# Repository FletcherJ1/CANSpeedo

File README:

Purpose
OBD Case (ebay link / picture)
Picture of PCB design
Costs
Firmware etc
Hardware used.
Libraries used.
Picture of results
Open about current issues

Cars it currently works on

Instructions to use / get to work with car.

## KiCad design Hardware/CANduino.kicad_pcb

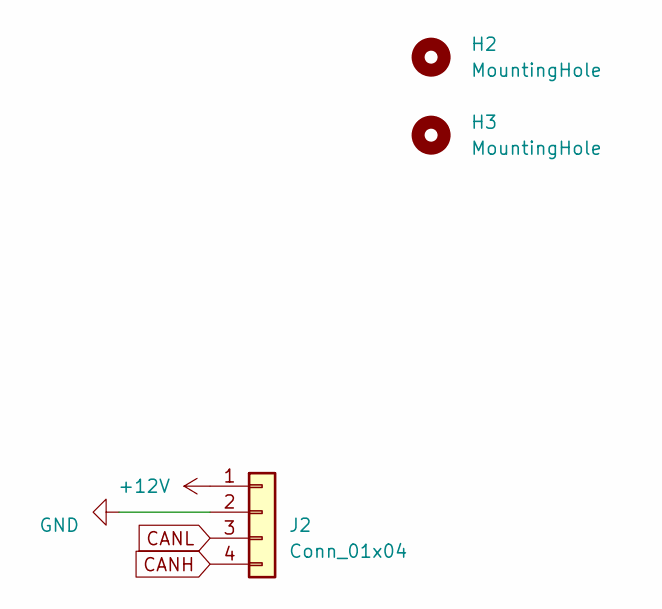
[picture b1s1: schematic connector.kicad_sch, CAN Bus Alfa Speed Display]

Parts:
H2, H3: MountingHole; MountingHole_6mm_Pad
J2: Conn_01x04; PinHeader_1x04_P1.27mm_Vertical

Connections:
+12V: J2.1; also elsewhere on the board
CANH: J2.4; also elsewhere on the board
CANL: J2.3; also elsewhere on the board
GND: J2.2; also elsewhere on the board

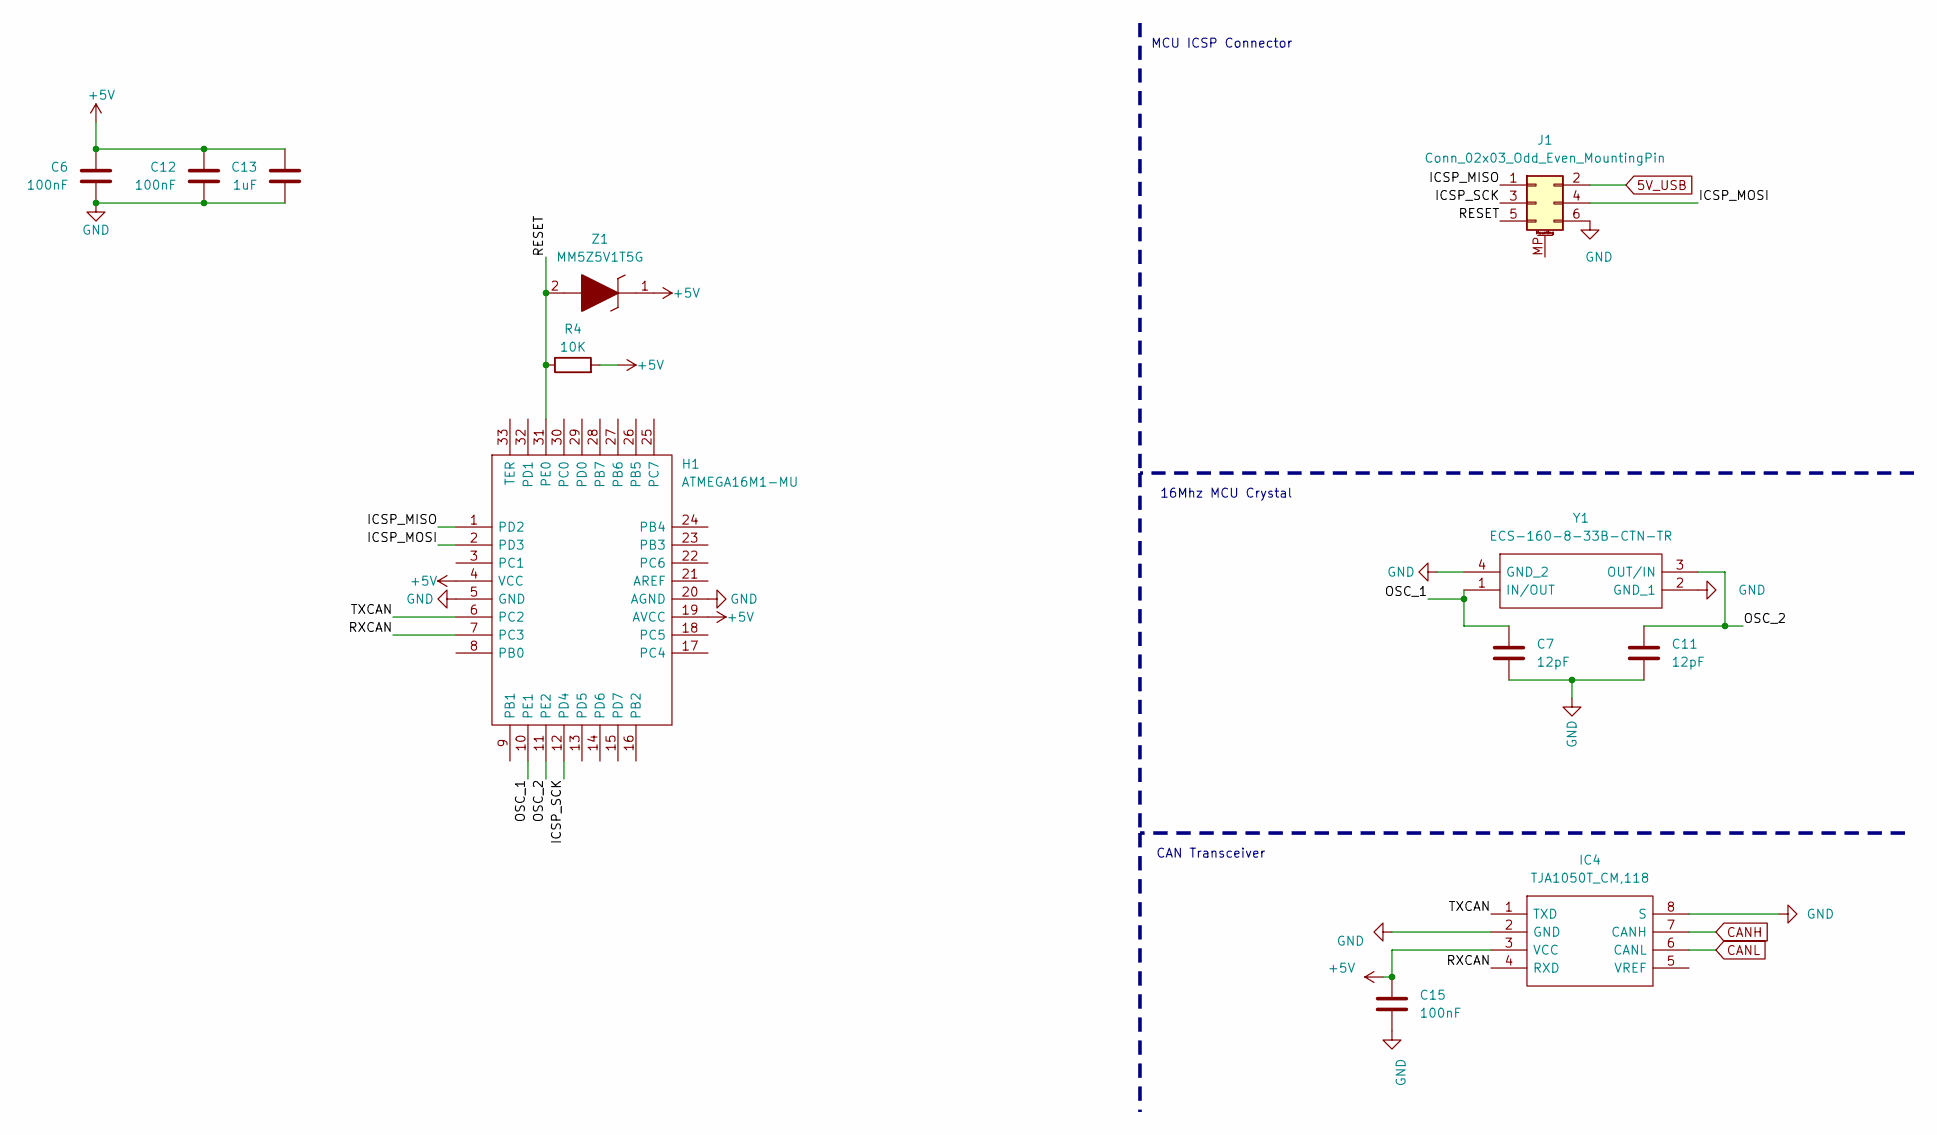
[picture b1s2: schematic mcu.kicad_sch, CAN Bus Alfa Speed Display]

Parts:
C6, C12, C15: 100nF; C_0603_1608Metric_Pad1.08x0.95mm_HandSolder
C7, C11: 12pF; C_0603_1608Metric_Pad1.08x0.95mm_HandSolder
C13: 1uF; C_0603_1608Metric_Pad1.08x0.95mm_HandSolder
H1: ATMEGA16M1-MU; QFN65P700X700X100-33N; Mouser Part Number 556-ATMEGA16M1-MU
IC4: TJA1050T_CM,118; SOIC127P600X175-8N; Mouser Part Number 771-TJA1050T/CM118
J1: Conn_02x03_Odd_Even_MountingPin; PinHeader_2x03_P2.54mm_Vertical
R4: 10K; R_0603_1608Metric_Pad0.98x0.95mm_HandSolder
Y1: ECS-160-8-33B-CTN-TR; ECS160833BCTNTR; Mouser Part Number 520-ECS160833BCTN-TR
Z1: MM5Z5V1T5G; SODFL1608X70N; Mouser Part Number 863-MM5Z5V1T5G

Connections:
5V_USB: J1.2; also elsewhere on the board
+5V: C6.2, C12.2, C13.2, C15.1, H1.4 (VCC), H1.19 (AVCC), IC4.3 (VCC), R4.2, Z1.1; also elsewhere on the board
/mcu/ICSP_MISO: H1.1 (PD2), J1.1
/mcu/ICSP_MOSI: H1.2 (PD3), J1.4
/mcu/ICSP_SCK: H1.12 (PD4), J1.3
/mcu/OSC_1: C7.1, H1.10 (PE1), Y1.1 (IN/OUT)
/mcu/OSC_2: C11.1, H1.11 (PE2), Y1.3 (OUT/IN)
/mcu/RESET: H1.31 (PE0), J1.5, R4.1, Z1.2
/mcu/RXCAN: H1.7 (PC3), IC4.4 (RXD)
/mcu/TXCAN: H1.6 (PC2), IC4.1 (TXD)
CANH: IC4.7 (CANH); also elsewhere on the board
CANL: IC4.6 (CANL); also elsewhere on the board
GND: C6.1, C7.2, C11.2, C12.1, C13.1, C15.2, H1.5 (GND), H1.20 (AGND), IC4.2 (GND), IC4.8 (S), J1.6, Y1.2 (GND_1), Y1.4 (GND_2); also elsewhere on the board

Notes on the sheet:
CAN Transceiver
MCU ICSP Connector
16Mhz MCU Crystal

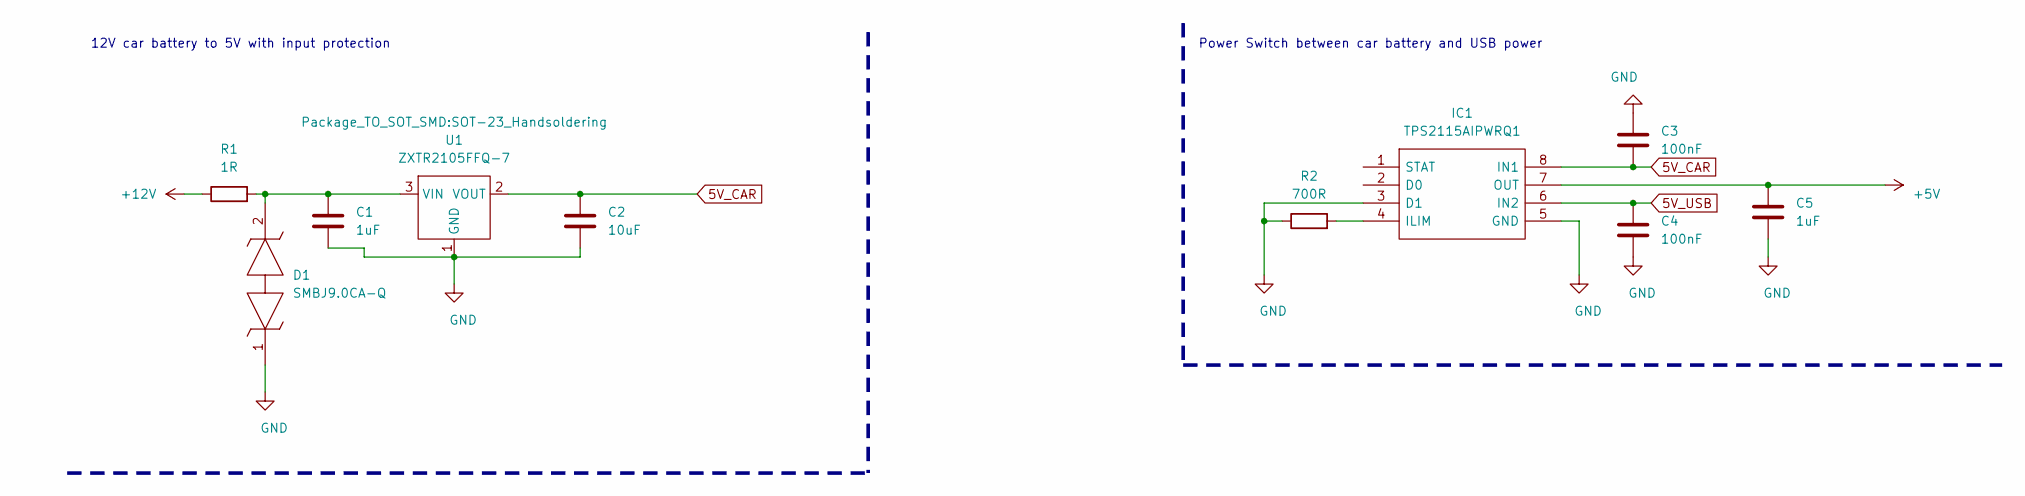
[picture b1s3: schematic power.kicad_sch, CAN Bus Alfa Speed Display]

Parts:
C1, C5: 1uF; C_0603_1608Metric_Pad1.08x0.95mm_HandSolder
C2: 10uF; C_0603_1608Metric_Pad1.08x0.95mm_HandSolder
C3, C4: 100nF; C_0603_1608Metric_Pad1.08x0.95mm_HandSolder
D1: SMBJ9.0CA-Q; DIONM5127X229N; Mouser Part Number 652-SMBJ9.0CA-Q
IC1: TPS2115AIPWRQ1; SOP65P640X120-8N; Mouser Part Number 595-TPS2115AIPWRQ1
R1: 1R; R_0603_1608Metric_Pad0.98x0.95mm_HandSolder
R2: 700R; R_0603_1608Metric_Pad0.98x0.95mm_HandSolder
U1: ZXTR2105FFQ-7; SOT-23_Handsoldering

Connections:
5V_CAR: C2.1, C3.2, IC1.8 (IN1), U1.2 (VOUT)
5V_USB: C4.1, IC1.6 (IN2); also elsewhere on the board
+5V: C5.1, IC1.7 (OUT); also elsewhere on the board
+12V: R1.1; also elsewhere on the board
GND: C1.2, C2.2, C3.1, C4.2, C5.2, D1.1, IC1.3 (D1), IC1.5 (GND), R2.1, U1.1 (GND); also elsewhere on the board
unnamed: C1.1, D1.2, R1.2, U1.3 (VIN)
unnamed: IC1.4 (ILIM), R2.2

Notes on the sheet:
12V car battery to 5V with input protection
Power Switch between car battery and USB power

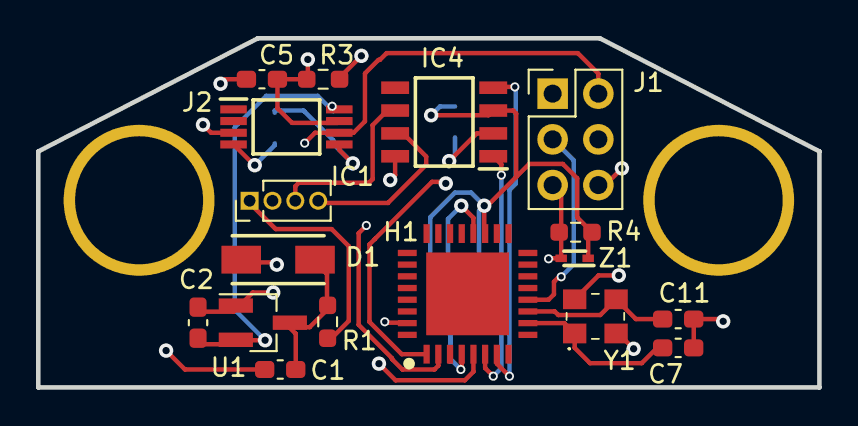
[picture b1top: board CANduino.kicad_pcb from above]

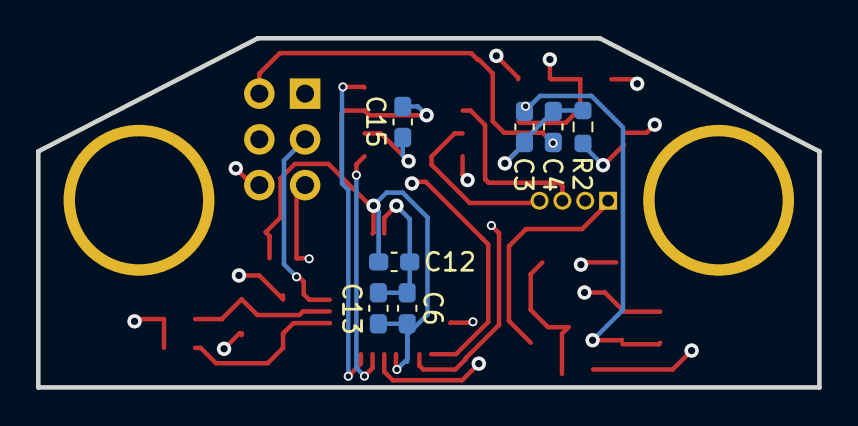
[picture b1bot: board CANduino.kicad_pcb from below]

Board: 4 copper layers, 43.4 x 19.4 mm, 26 parts (7 on the bottom side), 17 nets.

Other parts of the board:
R3: 50R; R_0603_1608Metric_Pad0.98x0.95mm_HandSolder

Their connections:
+5V: R3.1; also elsewhere on the board
GND: R3.2; also elsewhere on the board

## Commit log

2021-07-13 First commit - code and harware design provided
2021-07-13 Removed backup files for Kicad
2021-07-13 Added LICENSE file
2021-07-13 Cleaned up comments in code
2021-07-13 Added picture of obd plug and updated README
2021-07-13 Added CAN msg data dumps with update in README
2021-07-13 Added picture of PCB design and updated README
2021-07-13 Changed SVG to JPG due to browser rendering wrong
2021-07-13 Added pictures of result and pcb in case
2021-07-13 Fix filename mistake and resized image
2021-07-13 This should fix image resize
2021-07-13 Centered image
2021-07-14 Fixed mistake in README
2021-07-14 Fixed error in README
